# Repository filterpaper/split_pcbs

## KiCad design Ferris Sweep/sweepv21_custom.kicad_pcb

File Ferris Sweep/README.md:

# Modified Ferris Sweep PCBs

Minimal Ferris [Sweepv2.1](https://github.com/davidphilipbarr/Sweep/tree/main/Sweepv2) and [Half-swept](https://github.com/davidphilipbarr/Sweep/tree/main/Sweep-half-swept) are modified with the following changes:
* Removed mascot, puck and battery support
* Removed reset switch on half-swept
* Corrected MCU pin labels and alignment
* Added switch silkscreen from Pierre's [Ferris v0.1](https://github.com/pierrechevalier83/ferris/tree/main/0.1)

Custom Ferris [Sweepv2](https://github.com/davidphilipbarr/Sweep/tree/main/Sweepv2) are modified with the following changes:
* Removed mascot, puck and battery support
* Corrected MCU pin lables and alignment

## How To Build
See David Barr's [Sweep](https://github.com/davidphilipbarr/Sweep) page for instructions.

## Designed By
* [Pierre Chevalier](https://github.com/pierrechevalier83/ferris/)
* [David Barr](https://github.com/davidphilipbarr/Sweep/)
* [Ibnu Daru Aji](https://github.com/ibnuda/)

## Renders

### Sweepv2.1

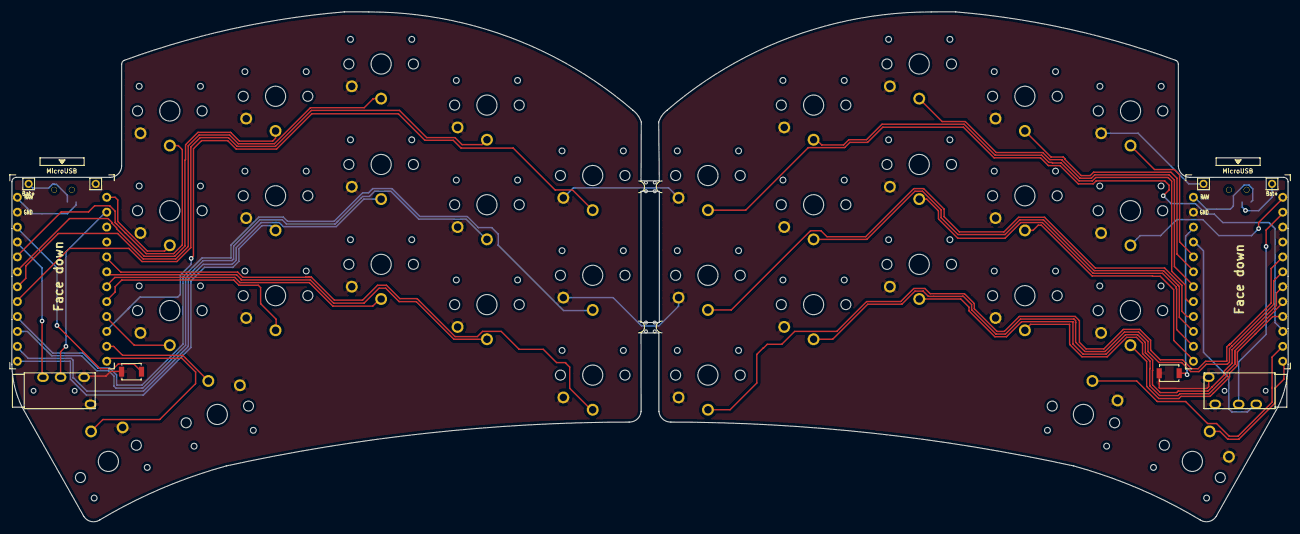
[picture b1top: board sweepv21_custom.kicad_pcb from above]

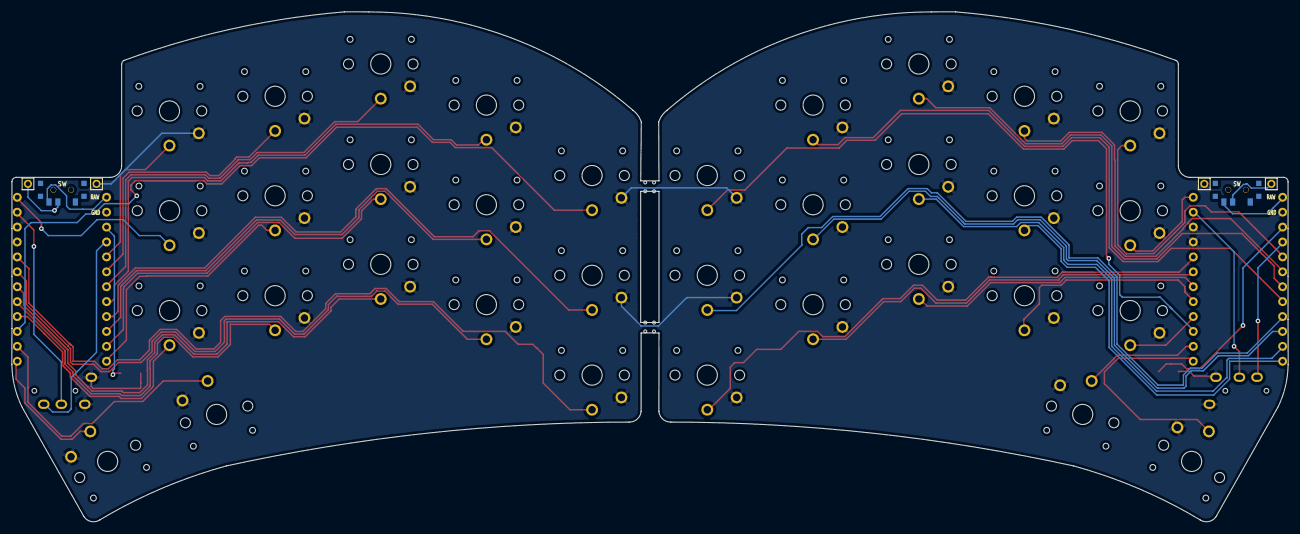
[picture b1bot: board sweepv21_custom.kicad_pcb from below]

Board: 2 copper layers, 217.4 x 86.9 mm, 48 parts (2 on the bottom side), 43 nets.

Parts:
 : MountingHole_Pad; 1pin_conn
 #2: MountingHole_Pad; 1pin_conn
Bat+: MountingHole_Pad; 1pin_conn
Bat+#2: MountingHole_Pad; 1pin_conn
J1, J2: AudioJack4dpb; TRRS-PJ-320A
RSW1, RSW2: SW_Push; SW_SPST_B3U-1000P
SW: SW_SPDT; SPDT_C128955
SW2, SW2_r1, SW3, SW3_r1, SW4, SW4_r1, SW5, SW5_r1, SW6, SW6_r1, SW7_r1, SW8, SW8_r1, SW9, SW9_r1, SW11, SW11_r1, SW12, SW12_r1, SW13_r1, SW14, SW15, SW15_r1, SW16, SW16_r1, SW17, SW17_r1, SW18, SW18_r1, SW20, SW20_r1, SW21, SW21_r1: SW_Push; SW_PG1350_nonrev_DPB
SW10: SW_Push; SW_PG1350_rev_DPB
SW#2: SW_SPDT; SPDT_C128955
U1, U2: ProMicro-kbd; ProMicro_v3_min
mouse-bite-2mm-slot, mouse-bite-2mm-slot#2: VAL**; mouse-bite-2mm-slot-with-space-for-track

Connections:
BT+: Bat+#2.1, SW#2.2
BT+_r: Bat+.1, SW.2
Switch1: SW2.1, U1.10
Switch1_r: SW2_r1.1, U2.10
Switch2: SW3.1, U1.17
Switch2_r: SW3_r1.1, U2.17
Switch3: SW4.1, U1.18
Switch3_r: SW4_r1.1, U2.18
Switch4: SW5.1, U1.19
Switch4_r: SW5_r1.1, U2.19
Switch5: SW6.1, U1.20
Switch5_r: SW6_r1.1, U2.20
Switch6: SW8.1, U1.16
Switch6_r: SW7_r1.1, U2.16
Switch7: SW9.1, U1.15
Switch7_r: SW8_r1.1, U2.15
Switch8: SW10.1, U1.14
Switch8_r: SW9_r1.1, U2.14
Switch9: SW11.1, U1.13
Switch9_r: SW11_r1.1, U2.13
Switch10: SW12.1, U1.1
Switch10_r: SW12_r1.1, U2.1
Switch11: SW14.1, U1.5
Switch11_r: SW13_r1.1, U2.5
Switch12: SW15.1, U1.6
Switch12_r: SW18_r1.1, U2.6
Switch13: SW16.1, U1.7
Switch13_r: SW15_r1.1, U2.7
Switch14: SW17.1, U1.8
Switch14_r: SW16_r1.1, U2.8
Switch15: SW18.1, U1.9
Switch15_r: SW17_r1.1, U2.9
Switch16: SW21.1, U1.11
Switch16_r: SW21_r1.1, U2.11
Switch17: SW20.1, U1.12
Switch17_r: SW20_r1.1, U2.12
Switch18: J2.R1, U1.2
Switch18_r: J1.R1, U2.2
gnd: .1, #2.1, J1.S, J1.T, J2.S, J2.T, RSW1.1, RSW2.1, SW2.2, SW2_r1.2, SW3.2, SW3_r1.2, SW4.2, SW4_r1.2, SW5.2, SW5_r1.2, SW6.2, SW6_r1.2, SW7_r1.2, SW8.2, SW8_r1.2, SW9.2, SW9_r1.2, SW10.2, SW11.2, SW11_r1.2, SW12.2, SW12_r1.2, SW13_r1.2, SW14.2, SW15.2, SW15_r1.2, SW16.2, SW16_r1.2, SW17.2, SW17_r1.2, SW18.2, SW18_r1.2, SW20.2, SW20_r1.2, SW21.2, SW21_r1.2, U1.3, U1.4, U1.23, U2.3, U2.4, U2.23
raw: SW.3, SW#2.3, U1.24, U2.24
reset: RSW1.2, U1.22
reset_r: RSW2.2, U2.22
vcc: J1.R2, J2.R2, U1.21, U2.21

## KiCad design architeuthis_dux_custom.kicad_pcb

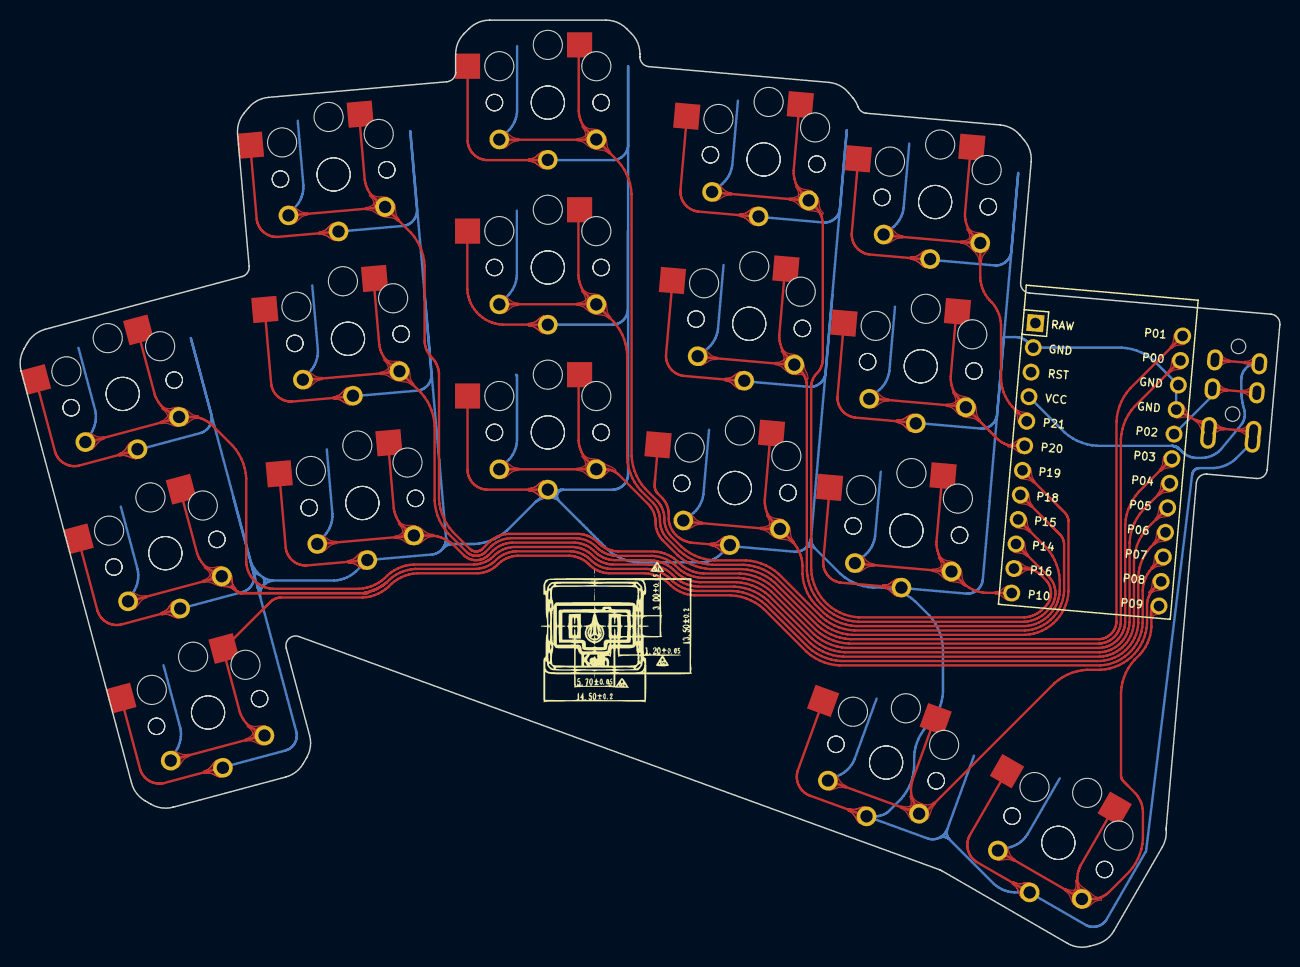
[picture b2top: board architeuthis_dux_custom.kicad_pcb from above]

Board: 2 copper layers, 129.9 x 95.6 mm, 36 parts (0 on the bottom side), 20 nets.

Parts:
C1: ProMicro
S1, S2, S3, S4, S5, S6, S7, S8, S9, S10, S11, S12, S13, S14, S15, S16, S17, S18, S19, S20, S21, S22, S23, S24, S25, S26, S27, S28, S29, S30, S31, S32, S33, S34: PG1350
T1: TRRS-PJ-320A-dual

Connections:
GND: C1.2, C1.15, C1.16, S1.2, S2.2, S3.2, S4.2, S5.2, S6.2, S7.2, S8.2, S9.2, S10.2, S11.2, S12.2, S13.2, S14.2, S15.2, S16.2, S17.2, S18.2, S19.2, S20.2, S21.2, S22.2, S23.2, S24.2, S25.2, S26.2, S27.2, S28.2, S29.2, S30.2, S31.2, S32.2, S33.2, S34.2, T1.1, T1.2
P0: C1.14, S11.1, S12.1
P1: C1.13, S13.1, S14.1
P2: C1.17, T1.3
P3: C1.18, S9.1, S10.1
P4: C1.19, S7.1, S8.1
P5: C1.20, S5.1, S6.1
P6: C1.21, S3.1, S4.1
P7: C1.22, S1.1, S2.1
P8: C1.23, S31.1, S32.1
P9: C1.24, S33.1, S34.1
P10: C1.12, S25.1, S26.1
P14: C1.10, S21.1, S22.1
P15: C1.9, S19.1, S20.1
P16: C1.11, S23.1, S24.1
P18: C1.8, S17.1, S18.1
P19: C1.7, S15.1, S16.1
P20: C1.6, S27.1, S28.1
P21: C1.5, S29.1, S30.1
VCC: C1.4, T1.4
